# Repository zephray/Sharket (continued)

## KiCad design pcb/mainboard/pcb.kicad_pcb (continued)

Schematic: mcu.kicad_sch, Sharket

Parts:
C201: 2.2nF; C_0402_1005Metric
C202, C203, C206, C207, C212, C213, C217, C219, C223, C225, C228, C231, C234, C235, C237, C238, C241, C243, C244, C246: 220nF; C_0201_0603Metric
C204: 4.7uF; C_0402_1005Metric
C205, C208, C209, C211, C216, C222, C240, C248, C249, C250: 10uF; C_0402_1005Metric
C210, C214, C215, C220, C221, C226, C227, C229, C230, C232, C233, C236, C239, C242, C245, C247, C251, C252, C253, C254, C255: 1uF; C_0201_0603Metric
C218, C224: 18pF; C_0402_1005Metric
R201, R204, R205, R206, R207: 10K; R_0402_1005Metric
R202: 100K/1%; R_0402_1005Metric
R203, R804: 100K; R_0402_1005Metric; LCSC C93929
SW201: SW_Push; SW_SPST_SKQG_WithStem
U201: MIMX8MN6DVTJZAA; BGA-486_27x27_14.0x14.0mm
Y201: 24MHz; Oscillator_SMD_Abracon_ASE-4Pin_3.2x2.5mm

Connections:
+1V1: C248.1, C249.1, C250.1, C251.1, C252.1, C253.1, C254.1, C255.1, U201.K8 (NVCC_DRAM), U201.K9 (NVCC_DRAM), U201.L9 (NVCC_DRAM), U201.M9 (NVCC_DRAM), U201.N8 (NVCC_DRAM), U201.N9 (NVCC_DRAM), U201.P7 (NVCC_DRAM), U201.R8 (NVCC_DRAM), U201.R9 (NVCC_DRAM), U201.T9 (NVCC_DRAM), U201.U9 (NVCC_DRAM), U201.V8 (NVCC_DRAM), U201.V9 (NVCC_DRAM); also elsewhere on the board
+1V2: C202.1, U201.J15 (VDD_MIPI_1P2); also elsewhere on the board
+1V8: C208.1, C213.1, C219.1, C225.1, C228.1, C231.1, C234.1, C237.1, C246.1, U201.AB13 (PVCC_1P8), U201.H10 (NVCC_ECSPI), U201.J11 (NVCC_I2C), U201.J12 (NVCC_UART), U201.J13 (PVCC_1P8), U201.L19 (NVCC_JTAG), U201.M19 (NVCC_CLK), U201.T19 (PVCC_1P8), U201.U19 (NVCC_NAND), U201.V19 (NVCC_SAI2), U201.V20 (NVCC_SD1), U201.W12 (NVCC_GPIO1), U201.W17 (NVCC_SAI5), U201.W22 (NVCC_ENET), U201.Y10 (NVCC_SAI3); also elsewhere on the board
+1V8A: C205.1, C207.1, C212.1, C217.1, C223.1, C235.1, C238.1, U201.AA14 (VDD_ANA0_1P8), U201.H13 (VDD_MIPI_1P8), U201.H15 (VDD_USB_1P8), U201.N19 (VDD_24M_XTAL_1P8), U201.N20 (VDD_ANA1_1P8), U201.P5 (VDD_DRAM_PLL_1P8), U201.P19 (VDD_ANA1_1P8), U201.R19 (VDD_ARM_PLL_1P8), U201.Y15 (VDD_ANA0_1P8); also elsewhere on the board
+3V3: C240.1, C243.1, U201.K19 (VDD_USB_3P3); also elsewhere on the board
+VCCIO_SD: U201.V22 (NVCC_SD2); also elsewhere on the board
CLK_32K_OUT: U201.A26 (RTC_XTALI); also elsewhere on the board
GND: C201.2, C202.2, C203.2, C204.2, C205.2, C206.2, C207.2, C208.2, C209.2, C210.2, C211.2, C212.2, C213.2, C214.2, C215.2, C216.2, C217.2, C218.2, C219.2, C220.2, C221.2, C222.2, C223.2, C224.2, C225.2, C226.2, C227.2, C228.2, C229.2, C230.2, C231.2, C232.2, C233.2, C234.2, C235.2, C236.2, C237.2, C238.2, C239.2, C240.2, C241.2, C242.2, C243.2, C244.2, C245.2, C246.2, C247.2, C248.2, C249.2, C250.2, C251.2, C252.2, C253.2, C254.2, C255.2, R201.1, R202.1, R204.1, R207.1, SW201.2, U201.A1 (VSS), U201.A27 (VSS), U201.AA7 (VSS), U201.AA9 (VSS), U201.AA10 (VSS), U201.AA13 (VSS), U201.AA15 (VSS), U201.AA18 (VSS), U201.AA19 (VSS), U201.AA21 (VSS), U201.AB3 (VSS), U201.AB25 (VSS), U201.AC3 (VSS), U201.AC25 (VSS), U201.AE2 (VSS), U201.AE5 (VSS), U201.AE6 (VSS), U201.AE9 (VSS), U201.AE10 (VSS), U201.AE13 (VSS), U201.AE14 (VSS), U201.AE15 (VSS), U201.AE18 (VSS), U201.AE19 (VSS), U201.AE22 (VSS), U201.AE23 (VSS), U201.AF3 (VSS), U201.AG1 (VSS), U201.AG27 (VSS), U201.B3 (VSS), U201.B26 (VSS), U201.C2 (VSS), U201.C5 (VSS), U201.C6 (VSS), U201.C9 (VSS), U201.C10 (VSS), U201.C13 (VSS), U201.C14 (VSS), U201.C15 (VSS), U201.C18 (VSS), U201.C19 (VSS), U201.C22 (VSS), U201.C23 (VSS), U201.E3 (VSS), U201.E25 (VSS), U201.F3 (VSS), U201.F25 (VSS), U201.G7 (VSS), U201.G9 (VSS), U201.G10 (VSS), U201.G13 (VSS), U201.G15 (VSS), U201.G18 (VSS), U201.G19 (VSS), U201.G21 (VSS), U201.H2 (VSS), U201.H18 (VSS), U201.J3 (VSS), U201.J7 (VSS), U201.J21 (VSS), U201.J25 (VSS), U201.K3 (VSS), U201.K7 (VSS), U201.K20 (VSS), U201.K21 (VSS), U201.K25 (VSS), U201.L12 (VSS), U201.L16 (VSS), U201.M12 (VSS), U201.M16 (VSS), U201.N3 (VSS), U201.N7 (VSS), U201.N12 (VSS), U201.N16 (VSS), U201.N21 (VSS), U201.N25 (VSS), U201.P3 (VSS), U201.P13 (VSS), U201.P15 (VSS), U201.P21 (VSS), U201.P25 (VSS), U201.R3 (VSS), U201.R7 (VSS), U201.R12 (VSS), U201.R16 (VSS), U201.R20 (VSS), U201.R21 (VSS), U201.R25 (VSS), U201.T12 (VSS), U201.T16 (VSS), U201.U12 (VSS), U201.U16 (VSS), U201.V3 (VSS), U201.V7 (VSS), U201.V21 (VSS), U201.V25 (VSS), U201.W3 (VSS), U201.W7 (VSS), U201.W21 (VSS), U201.W25 (VSS), U201.Y2 (VSS), U201.Y13 (VSS), U201.Y18 (VSS), Y201.2, Y201.4; also elsewhere on the board
JTAG_TCK: U201.F26 (JTAG_TCK); also elsewhere on the board
JTAG_TDI: U201.E27 (JTAG_TDI); also elsewhere on the board
JTAG_TDO: U201.E26 (JTAG_TDO); also elsewhere on the board
JTAG_TMS: U201.F27 (JTAG_TMS); also elsewhere on the board
unnamed: C218.1, U201.B27 (24M_XTALI), Y201.1
unnamed: C224.1, U201.C26 (24M_XTALO), Y201.3
unnamed: R204.2, U201.G26 (BOOT_MODE0)
unnamed: R205.2, U201.G27 (BOOT_MODE1)
unnamed: R206.2, SW201.1, U201.C27 (BOOT_MODE2)
unnamed: R207.2, U201.D26 (BOOT_MODE3)
unnamed: R201.2, U201.D27 (JTAG_MOD)
unnamed: R202.2, U201.J24 (TSENSOR_RES_EXT)
unnamed: C201.1, U201.D15 (MIPI_VREG_CAP)
ONOFF: R203.1, U201.A25 (ONOFF); also elsewhere on the board
PMIC_ON_REQ: U201.A24 (PMIC_ON_REQ); also elsewhere on the board
PMIC_STBY_REQ: U201.E24 (PMIC_STBY_REQ); also elsewhere on the board
POR_B: R804.1, U201.B24 (POR_B); also elsewhere on the board
RTC_0P8: C244.1, U201.B25 (RTC_XTALO), U201.K22 (VDD_SNVS_0P8); also elsewhere on the board
RTC_1P8: C241.1, R203.2, R205.1, R206.1, R804.2, U201.J22 (NVCC_SNVS_1P8); also elsewhere on the board
RTC_RESET_B: U201.F24 (RTC_RESET_B); also elsewhere on the board
VDD_ARM: C209.1, C214.1, C220.1, C226.1, C229.1, C232.1, U201.R13 (VDD_ARM), U201.R15 (VDD_ARM), U201.T13 (VDD_ARM), U201.T14 (VDD_ARM), U201.T15 (VDD_ARM), U201.U13 (VDD_ARM), U201.U15 (VDD_ARM), U201.V13 (VDD_ARM), U201.V15 (VDD_ARM), U201.V16 (VDD_ARM), U201.W13 (VDD_ARM), U201.W14 (VDD_ARM), U201.W15 (VDD_ARM), U201.W16 (VDD_ARM); also elsewhere on the board
VDD_SOC: C203.1, C204.1, C206.1, C210.1, C211.1, C215.1, C216.1, C221.1, C222.1, C227.1, C230.1, C233.1, C236.1, C239.1, C242.1, C245.1, C247.1, U201.J10 (VDD_DRAM), U201.J14 (VDD_MIPI_0P8), U201.J17 (VDD_USB_0P8), U201.K15 (VDD_SOC), U201.K16 (VDD_SOC), U201.L10 (VDD_DRAM), U201.L15 (VDD_SOC), U201.L17 (VDD_ANA_0P8), U201.L18 (VDD_SOC), U201.M15 (VDD_SOC), U201.N10 (VDD_DRAM), U201.N13 (VDD_SOC), U201.N15 (VDD_SOC), U201.N17 (VDD_ANA_0P8), U201.N18 (VDD_SOC), U201.P9 (VDD_DRAM_PLL_0P8), U201.P12 (VCC_GPU), U201.P16 (VDD_ARM_PLL_0P8), U201.R10 (VDD_DRAM), U201.R11 (VCC_GPU), U201.R17 (VDD_SOC), U201.R18 (VDD_SOC), U201.U10 (VDD_DRAM), U201.U11 (VCC_GPU), U201.U17 (VDD_SOC), U201.U18 (VDD_SOC), U201.V12 (VCC_GPU), U201.W10 (VDD_DRAM), U201.W11 (VCC_GPU); also elsewhere on the board

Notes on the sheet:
QSPI boot by default, press button changes to eMMC boot (invalid) so it should fallback to USB
0201
PLL
VDDQ
0402
NVCC PVCC
PLL ANA
XTAL

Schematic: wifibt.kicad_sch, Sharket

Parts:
ANT901: Conn_01x02; Texas_SWRA117D_2.4GHz_Right
C901, C902: 18pF; C_0402_1005Metric
C903, C906: DNP; C_0402_1005Metric
C904, C908: 100nF; C_0201_0603Metric
C905, C907, C909: 10uF; C_0603_1608Metric
L901: 4.7uH; L_1210_3225Metric
R901: 22; R_0402_1005Metric
R902: 0; R_0402_1005Metric
U901: AP6330(BCM4330); RL-SM02BD(RTL8723BS)
Y901: 26MHz; Oscillator_SMD_Abracon_ASE-4Pin_3.2x2.5mm

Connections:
+1V8: C908.1, C909.1, U901.22 (VDD_IO); also elsewhere on the board
+BATT: C904.1, C907.1, U901.9 (VBAT); also elsewhere on the board
BT_SHUTDOWN: U901.34 (BT_RST_N); also elsewhere on the board
GND: ANT901.2, C901.2, C902.2, C903.1, C904.2, C905.2, C906.1, C907.2, C908.2, C909.2, U901.1 (GND), U901.3 (GND), U901.20 (GND), U901.31 (GND), U901.33 (GND), U901.36 (GND), Y901.2, Y901.4; also elsewhere on the board
unnamed: ANT901.1, C906.2, R902.1
unnamed: C902.1, R901.1, Y901.1
unnamed: C905.1, L901.2, U901.23 (VIN_LDO)
unnamed: L901.1, U901.21 (VIN_LDO_OUT)
unnamed: C903.2, R902.2, U901.2 (WIFI/BT_ANT)
unnamed: C901.1, U901.10 (XTAL_IN), Y901.3
unnamed: R901.2, U901.11 (XTAL_OUT)
REF_CLK_32K: U901.24 (LPO); also elsewhere on the board
SD1_CLK: U901.17 (SD_CLK); also elsewhere on the board
SD1_CMD: U901.16 (SD_CMD); also elsewhere on the board
SD1_DATA0: U901.18 (SD_D0); also elsewhere on the board
SD1_DATA1: U901.19 (SD_D1); also elsewhere on the board
SD1_DATA2: U901.14 (SD_D2); also elsewhere on the board
SD1_DATA3: U901.15 (SD_D3); also elsewhere on the board
UART1_CTS: U901.44 (UART_CTS); also elsewhere on the board
UART1_RTS: U901.41 (UART_RTS); also elsewhere on the board
UART1_RXD: U901.42 (UART_TXD); also elsewhere on the board
UART1_TXD: U901.43 (UART_RXD); also elsewhere on the board
WL_PMU_EN: U901.12 (WL_REG_ON); also elsewhere on the board
WL_WAKE_AP: U901.13 (WL_HOST_WAKE); also elsewhere on the board

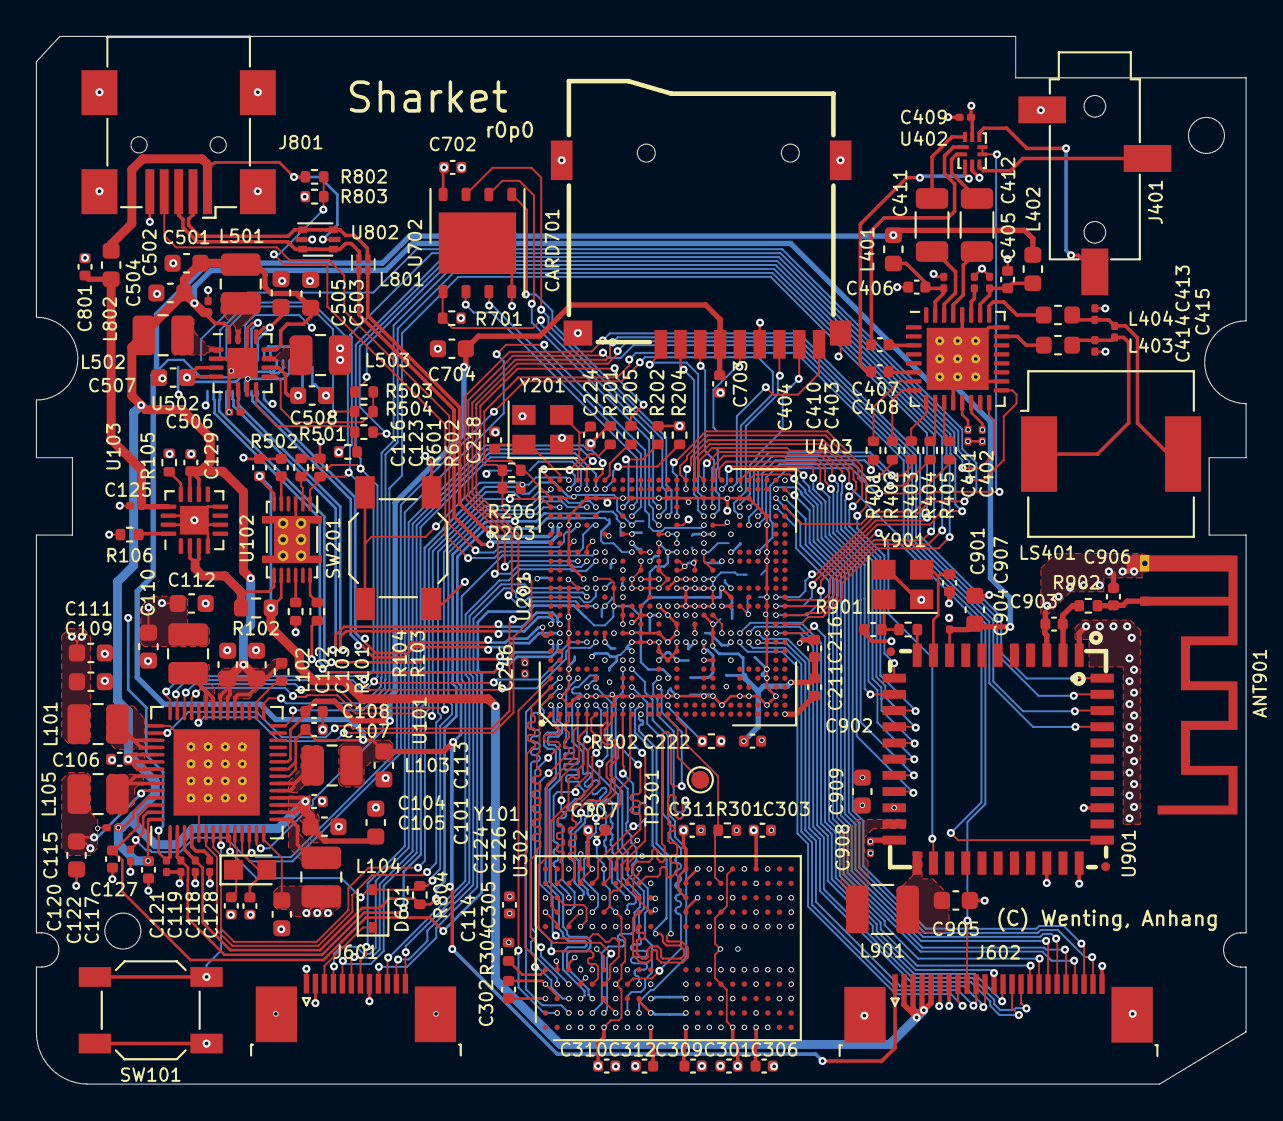
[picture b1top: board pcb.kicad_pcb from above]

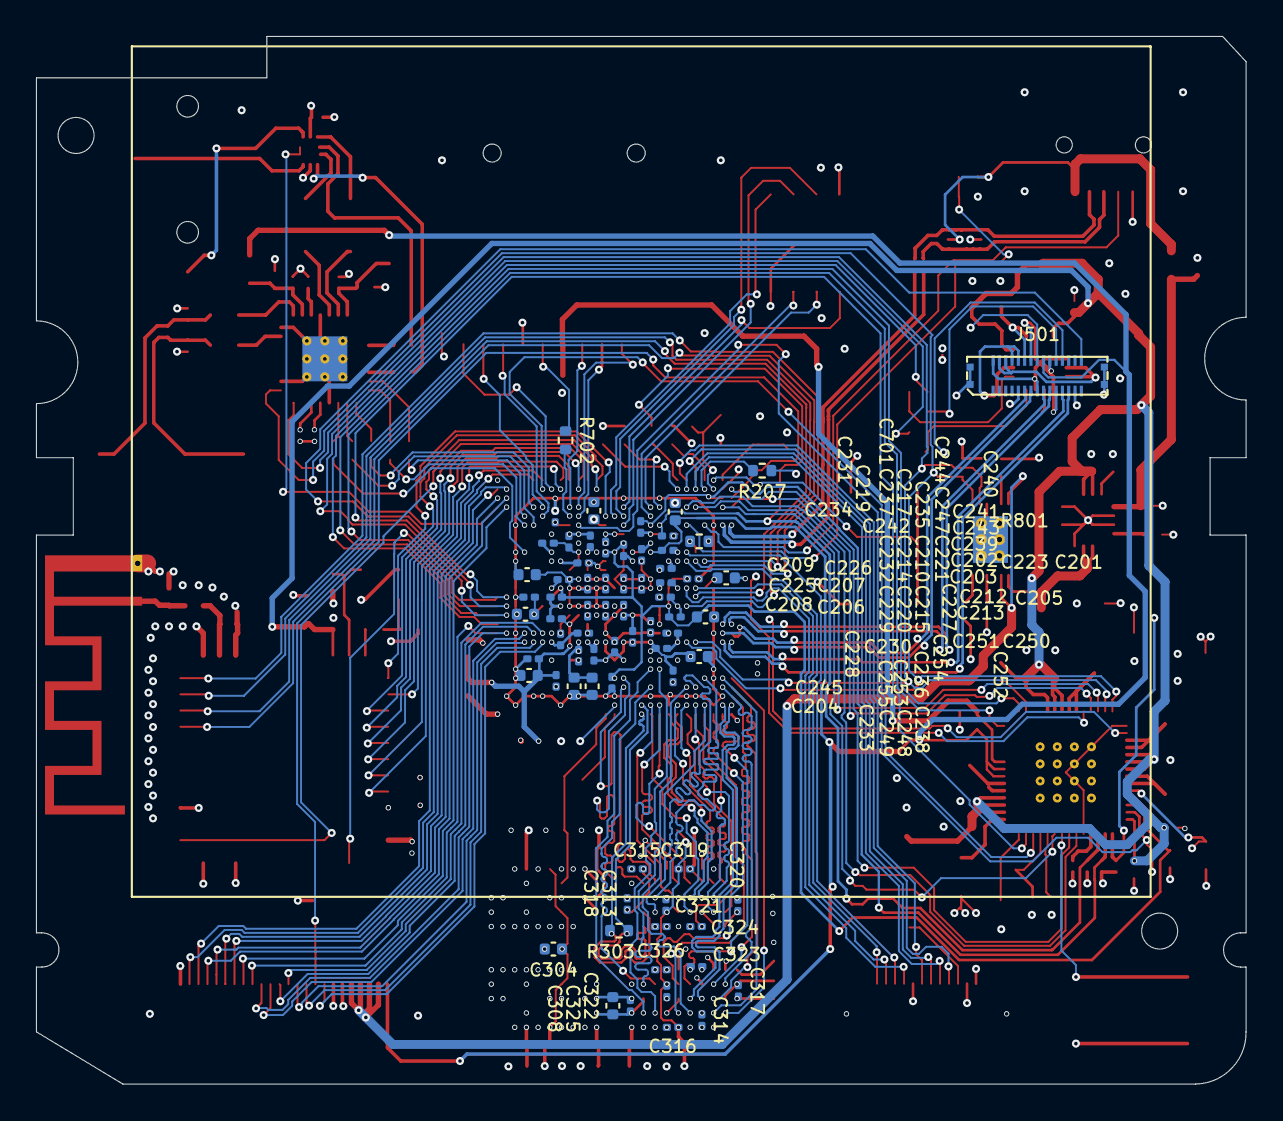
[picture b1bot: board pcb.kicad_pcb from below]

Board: 4 copper layers, 67.2 x 58.2 mm, 224 parts (71 on the bottom side), 204 nets.

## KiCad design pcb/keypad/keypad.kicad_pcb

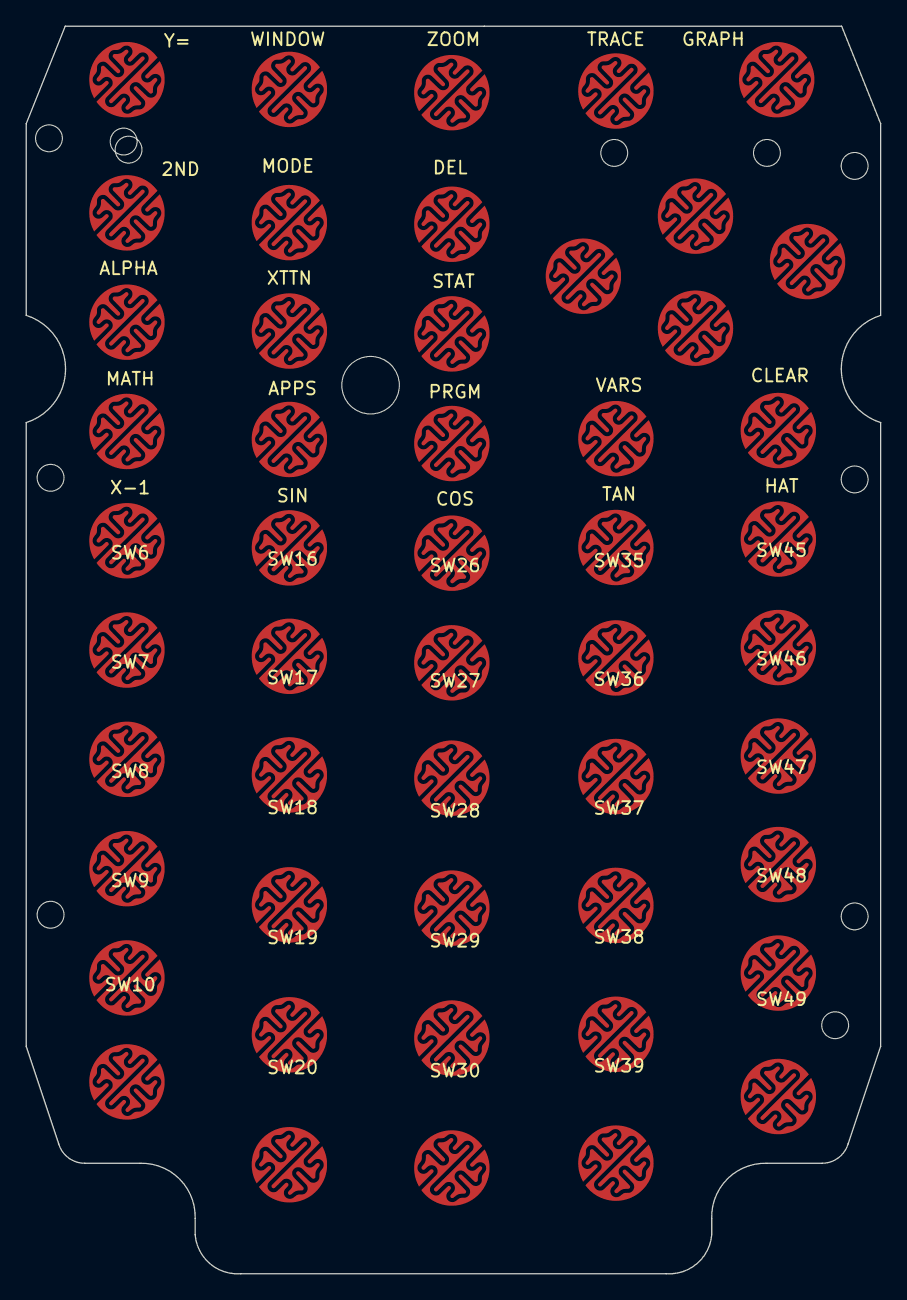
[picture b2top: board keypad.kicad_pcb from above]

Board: 2 copper layers, 66.8 x 97.5 mm, 50 parts (0 on the bottom side), 15 nets, no tracks yet.

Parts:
SW1: Y=; key2
SW2: 2ND; key2
SW3: ALPHA; key2
SW4: MATH; key2
SW5: X-1; key2
SW6: X2; key2
SW7: LOG; key2
SW8: LN; key2
SW9: STO; key2
SW10: ON; key2
SW11: WINDOW; key2
SW12: MODE; key2
SW13: XTTN; key2
SW14: APPS; key2
SW15: SIN; key2
SW16: COMMA; key2
SW17: 7; key2
SW18: 4; key2
SW19: 1; key2
SW20: 0; key2
SW21: ZOOM; key2
SW22: DEL; key2
SW23: STAT; key2
SW24: PRGM; key2
SW25: COS; key2
SW26: LBRACKET; key2
SW27: 8; key2
SW28: 5; key2
SW29: 2; key2
SW30: DOT; key2
SW31: L; key2
SW32: TRACE; key2
SW33: VARS; key2
SW34: TAN; key2
SW35: RBRACKET; key2
SW36: 9; key2
SW37: 6; key2
SW38: 3; key2
SW39: NEG; key2
SW40: U; key2
SW41: D; key2
SW42: GRAPH; key2
SW43: CLEAR; key2
SW44: HAT; key2
SW45: DIV; key2
SW46: MUL; key2
SW47: SUB; key2
SW48: ADD; key2
SW49: ENTER; key2
SW50: R; key2

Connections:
/Keys/KC0: SW1.2, SW2.2, SW11.2, SW12.2, SW21.2, SW22.1, SW32.2, SW42.2
/Keys/KC1: SW3.1, SW4.1, SW5.1, SW6.1, SW7.1, SW8.1, SW9.1
/Keys/KC2: SW13.1, SW14.1, SW15.1, SW16.1, SW17.1, SW18.1, SW19.1, SW20.1
/Keys/KC3: SW23.1, SW24.1, SW25.1, SW26.1, SW27.1, SW28.1, SW29.1, SW30.1
/Keys/KC4: SW33.1, SW34.1, SW35.1, SW36.1, SW37.1, SW38.1, SW39.1
/Keys/KC5: SW43.1, SW44.1, SW45.1, SW46.1, SW47.1, SW48.1, SW49.1
/Keys/KC6: SW31.2, SW40.2, SW41.1, SW50.1
/Keys/KR0: SW20.2, SW30.2, SW39.2, SW41.2, SW42.1, SW49.2
/Keys/KR1: SW9.2, SW19.2, SW29.2, SW31.1, SW32.1, SW38.2, SW48.2
/Keys/KR2: SW8.2, SW18.2, SW21.1, SW28.2, SW37.2, SW47.2, SW50.2
/Keys/KR3: SW7.2, SW11.1, SW17.2, SW27.2, SW36.2, SW40.1, SW46.2
/Keys/KR4: SW1.1, SW6.2, SW16.2, SW26.2, SW35.2, SW45.2
/Keys/KR5: SW2.1, SW5.2, SW15.2, SW25.2, SW34.2, SW44.2
/Keys/KR6: SW4.2, SW12.1, SW14.2, SW24.2, SW33.2, SW43.2
unnamed: SW3.2, SW13.2, SW22.2, SW23.2

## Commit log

2022-09-21 Keypad Layout v0
2022-09-21 Mainboard sch initial commit, wip
2022-09-22 Working on mainboard schematics
2022-09-23 Keypad Layout Done V1
2022-09-23 Mainboard schematics WIP
2022-09-24 Draft motherboard schematics for r0.0 layout
2022-09-24 Keypad Schematic Update - Comm Interface
2022-09-24 Motherboard PCB component initial placement, schematics fixes
2022-09-26 Routing mainboard in progress, schematics fixes
2022-09-27 Keypad Layout Update - JTAG/UART
2022-10-03 Update layout
2022-10-03 Minor - Layout wifi antenna
2022-10-04 Mainboard design bug fixes
2022-11-12 uboot Started
2023-03-07 Keypad bugfix, pulling in submodules
